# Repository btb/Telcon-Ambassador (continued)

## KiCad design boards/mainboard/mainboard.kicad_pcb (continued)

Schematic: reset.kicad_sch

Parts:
C26: C_Polarized_US; CP_Axial_L18.0mm_D10.0mm_P25.00mm_Horizontal
D17: 1N4148; D_DO-35_SOD27_P7.62mm_Horizontal
Q1, Q2, Q3: 2N3904; TO-92_Inline
R10, R11: 3.3K; R_Axial_DIN0309_L9.0mm_D3.2mm_P12.70mm_Horizontal
R12, R14: 680; R_Axial_DIN0309_L9.0mm_D3.2mm_P12.70mm_Horizontal
R13, R15: 150; R_Axial_DIN0309_L9.0mm_D3.2mm_P12.70mm_Horizontal
R171: 100; R_Axial_DIN0309_L9.0mm_D3.2mm_P12.70mm_Horizontal
R172: 47K; R_Axial_DIN0309_L9.0mm_D3.2mm_P12.70mm_Horizontal
U43: 7404; DIP-14_W7.62mm
U44: 12.5MHZ; Oscillator_DIP-14
U72: 7474; DIP-14_W7.62mm
U80: 7414; DIP-14_W7.62mm

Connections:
DBE: U80.4; also elsewhere on the board
GND: C26.2, Q1.1 (E), Q2.1 (E), Q3.1 (E), U44.7 (GND); also elsewhere on the board
unnamed: C26.1, D17.2 (A), Q1.2 (B), R171.1, R172.1
unnamed: Q1.3 (C), R10.2, R11.2, U80.11
unnamed: Q2.2 (B), R14.1
unnamed: Q3.2 (B), R12.1
unnamed: U43.13, U44.8 (OUT)
unnamed: R12.2, U72.5 (Q)
unnamed: R14.2, U72.6 (~Q), U80.1
OSC: U43.9, U43.11, U43.12; also elsewhere on the board
OSCB: U43.6; also elsewhere on the board
OSC/4: U72.3 (C); also elsewhere on the board
OSC/16: U72.2 (D); also elsewhere on the board
PHI1: Q2.3 (C), R15.2; also elsewhere on the board
PHI2: Q3.3 (C), R13.2; also elsewhere on the board
RESET: R11.1, U80.8; also elsewhere on the board
RESET_SW: R171.2; also elsewhere on the board
VCC: D17.1 (K), R10.1, R13.1, R15.1, R172.2, U44.14 (Vcc); also elsewhere on the board
~DBE: U80.2, U80.3; also elsewhere on the board
~OSCA: U43.10; also elsewhere on the board
~OSCB: U43.5, U43.8; also elsewhere on the board
~RESET: U80.9, U80.10; also elsewhere on the board

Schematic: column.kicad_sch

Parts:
RN3: 3.3K; R_Array_SIP10
U45: 74LS163; DIP-16_W7.62mm
U46: 74163; DIP-16_W7.62mm
U50: 7400; DIP-14_W7.62mm

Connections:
CBCLK: U46.7 (ENP), U46.10 (ENT); also elsewhere on the board
CC0: U46.14 (QA); also elsewhere on the board
CC1: U46.13 (QB); also elsewhere on the board
CC2: U46.12 (QC); also elsewhere on the board
CC3: U46.11 (QD); also elsewhere on the board
CC4: U45.14 (QA), U50.1; also elsewhere on the board
CC5: U45.13 (QB); also elsewhere on the board
CC6: U45.12 (QC), U50.2; also elsewhere on the board
GND: U45.3 (A), U45.4 (B), U45.5 (C), U45.6 (D), U45.8 (GND), U46.3 (A), U46.4 (B), U46.5 (C), U46.6 (D), U46.8 (GND); also elsewhere on the board
unnamed: RN3.5 (R4.2), U45.1 (~CLR), U46.1 (~CLR)
unnamed: U45.7 (ENP), U45.10 (ENT), U46.15 (RCO)
VCC: U45.16 (VCC), U46.16 (VCC); also elsewhere on the board
~OSCB: U45.2 (CLK), U46.2 (CLK); also elsewhere on the board
~POS79: U45.9 (~LOAD), U46.9 (~LOAD), U50.3; also elsewhere on the board

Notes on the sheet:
starts over from 0x00 at 01010000, 0x50, 80d

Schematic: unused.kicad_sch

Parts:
C1, C2, C3, C4, C5, C6, C7, C8, C9, C10, C11, C12, C13, C14, C15, C16, C17, C18, C19, C20, C21, C22, C27, C28, C29, C30, C31, C32, C33, C34, C35, C36, C37, C38, C39, C40, C41, C42, C43: 220nF; C_Disc_D4.3mm_W1.9mm_P6.35mm
RN3: 3.3K; R_Array_SIP10
RN4: R_Network09_Split; R_Array_SIP10
TP1: TestPoint; TestPoint_THTPad_1.0x1.0mm_Drill0.5mm
U10, U39, U53: 7408; DIP-14_W7.62mm
U11, U33, U50, U67: 7400; DIP-14_W7.62mm
U12, U43, U51, U75, U76: 7404; DIP-14_W7.62mm
U13, U14, U21: 74S139; DIP-16_W7.62mm
U34, U41, U63, U64, U65, U66, U72: 7474; DIP-14_W7.62mm
U38, U54: 7420; DIP-14_W7.62mm
U62: 7486; DIP-14_W7.62mm
U80: 7414; DIP-14_W7.62mm

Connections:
+12V: C15.1; also elsewhere on the board
-12V: C16.1; also elsewhere on the board
GND: C1.2, C2.2, C3.2, C4.2, C5.2, C6.2, C7.2, C8.2, C9.2, C10.2, C11.2, C12.2, C13.1, C14.2, C15.2, C16.2, C17.2, C18.2, C19.2, C20.1, C21.2, C22.2, C27.2, C28.1, C29.2, C30.2, C31.2, C32.2, C33.2, C34.2, C35.2, C36.2, C37.2, C38.2, C39.2, C40.2, C41.2, C42.2, C43.2, U10.7 (GND), U11.7 (GND), U12.7 (GND), U13.8 (GND), U14.8 (GND), U21.8 (GND), U33.7 (GND), U34.7 (GND), U38.7 (GND), U39.7 (GND), U41.7 (GND), U43.7 (GND), U50.7 (GND), U51.7 (GND), U53.7 (GND), U54.7 (GND), U62.7 (GND), U63.7 (GND), U64.7 (GND), U65.7 (GND), U66.7 (GND), U67.7 (GND), U72.7 (GND), U75.7 (GND), U76.7 (GND), U80.7 (GND); also elsewhere on the board
unnamed: RN3.10 (R9.2), TP1.1
VCC: C1.1, C2.1, C3.1, C4.1, C5.1, C6.1, C7.1, C8.1, C9.1, C10.1, C11.1, C12.1, C13.2, C14.1, C17.1, C18.1, C19.1, C20.2, C21.1, C22.1, C27.1, C28.2, C29.1, C30.1, C31.1, C32.1, C33.1, C34.1, C35.1, C36.1, C37.1, C38.1, C39.1, C40.1, C41.1, C42.1, C43.1, RN3.1 (R1.1), RN4.1 (R1.1), U10.14 (VCC), U11.14 (VCC), U12.14 (VCC), U13.16 (VCC), U14.16 (VCC), U21.16 (VCC), U33.14 (VCC), U34.14 (VCC), U38.14 (VCC), U39.14 (VCC), U41.14 (VCC), U43.14 (VCC), U50.14 (VCC), U51.14 (VCC), U53.14 (VCC), U54.14 (VCC), U62.14 (VCC), U63.14 (VCC), U64.14 (VCC), U65.14 (VCC), U66.14 (VCC), U67.14 (VCC), U72.14 (VCC), U75.14 (VCC), U76.14 (VCC), U80.14 (VCC); also elsewhere on the board

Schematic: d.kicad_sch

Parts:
RN1: R_Network09_US; R_Array_SIP10
U7: MC6800; DIP-40_W15.24mm
U8, U9: 74LS241; DIP-20_W7.62mm
U12: 7404; DIP-14_W7.62mm

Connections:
A0: U9.18 (O0a); also elsewhere on the board
A1: U9.3 (O3b); also elsewhere on the board
A2: U9.16 (O1a); also elsewhere on the board
A3: U8.3 (O3b); also elsewhere on the board
A4: U8.18 (O0a); also elsewhere on the board
A5: U9.14 (O2a); also elsewhere on the board
A6: U8.5 (O2b); also elsewhere on the board
A7: U8.16 (O1a); also elsewhere on the board
A8: U9.7 (O1b); also elsewhere on the board
A9: U8.7 (O1b); also elsewhere on the board
A10: U8.12 (O3a); also elsewhere on the board
A11: U8.9 (O0b); also elsewhere on the board
A12: U9.9 (O0b); also elsewhere on the board
A13: U9.12 (O3a); also elsewhere on the board
A14: U8.14 (O2a); also elsewhere on the board
A15: U9.5 (O2b); also elsewhere on the board
D0: U7.33 (D0); also elsewhere on the board
D1: U7.32 (D1); also elsewhere on the board
D2: U7.31 (D2); also elsewhere on the board
D3: U7.30 (D3); also elsewhere on the board
D4: U7.29 (D4); also elsewhere on the board
D5: U7.28 (D5); also elsewhere on the board
D6: U7.27 (D6); also elsewhere on the board
D7: U7.26 (D7); also elsewhere on the board
DBE: U7.36 (DBE); also elsewhere on the board
GND: U7.1 (VSS), U7.21 (VSS), U7.39 (TSC), U8.1 (OEa), U8.10 (GND), U9.1 (OEa), U9.10 (GND); also elsewhere on the board
unnamed: RN1.2 (R1), U7.2 (~HALT)
unnamed: RN1.6 (R5), U7.6 (~NMI)
unnamed: U7.9 (A0), U9.2 (I0a)
unnamed: U7.10 (A1), U9.17 (I3b)
unnamed: U7.11 (A2), U9.4 (I1a)
unnamed: U7.12 (A3), U8.17 (I3b)
unnamed: U7.13 (A4), U8.2 (I0a)
unnamed: U7.14 (A5), U9.6 (I2a)
unnamed: U7.15 (A6), U8.15 (I2b)
unnamed: U7.16 (A7), U8.4 (I1a)
unnamed: U7.17 (A8), U9.13 (I1b)
unnamed: U7.18 (A9), U8.13 (I1b)
unnamed: U7.19 (A10), U8.8 (I3a)
unnamed: U7.20 (A11), U8.11 (I0b)
unnamed: U7.22 (A12), U9.11 (I0b)
unnamed: U7.23 (A13), U9.8 (I3a)
unnamed: U7.24 (A14), U8.6 (I2a)
unnamed: U7.25 (A15), U9.15 (I2b)
unnamed: U7.34 (R/~W), U12.1
PHI1: U7.3 (Phi1); also elsewhere on the board
PHI2: U7.37 (Phi2); also elsewhere on the board
R/~W: U12.4; also elsewhere on the board
VCC: RN1.1 (common), U7.8 (VCC), U8.19 (OEb), U8.20 (VCC), U9.19 (OEb), U9.20 (VCC); also elsewhere on the board
VMA: U7.5 (VMA); also elsewhere on the board
~IRQ: RN1.4 (R3), U7.4 (~IRQ); also elsewhere on the board
~RESET: U7.40 (~RESET); also elsewhere on the board
~R/W: U12.2, U12.3; also elsewhere on the board

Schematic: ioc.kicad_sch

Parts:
D1: Conn_01x21; SolderWire-0.75sqmm_1x021_P3.96mm_D1.25mm_OD2.3mm
LS1: Speaker; Buzzer_15x7.5RM7.6
P1: Presets; DIP-16_W7.62mm
R2: 10; R_Axial_DIN0309_L9.0mm_D3.2mm_P12.70mm_Horizontal
R6, R7, R8: 220; R_Axial_DIN0309_L9.0mm_D3.2mm_P12.70mm_Horizontal
RN2: 3.3K; R_Array_SIP10
U70, U71: 6821; DIP-40_W15.24mm
U76: 7404; DIP-14_W7.62mm

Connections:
/IO/KBCON: D1.21, U70.39 (CA2)
/IO/KBD0: D1.12, U70.2 (PA0)
/IO/KBD1: D1.13, U70.3 (PA1)
/IO/KBD2: D1.14, U70.4 (PA2)
/IO/KBD3: D1.15, U70.5 (PA3)
/IO/KBD4: D1.16, U70.6 (PA4)
/IO/KBD5: D1.17, U70.7 (PA5)
/IO/KBD6: D1.18, U70.8 (PA6)
/IO/KBD7: D1.19, U70.9 (PA7)
/IO/KBINT: D1.20, U70.40 (CA1)
/IO/PA0: P1.4, RN2.2 (R1), U71.2 (PA0)
/IO/PRCON: D1.11, U70.19 (CB2)
/IO/PRD0: D1.2, U70.10 (PB0)
/IO/PRD1: D1.3, U70.11 (PB1)
/IO/PRD2: D1.4, U70.12 (PB2)
/IO/PRD3: D1.5, U70.13 (PB3)
/IO/PRD4: D1.6, U70.14 (PB4)
/IO/PRD5: D1.7, U70.15 (PB5)
/IO/PRD6: D1.8, U70.16 (PB6)
/IO/PRD7: D1.9, U70.17 (PB7)
/IO/PRINT: D1.10, U70.18 (CB1)
A0: U70.36 (RS0), U71.36 (RS0); also elsewhere on the board
A1: U70.35 (RS1), U71.35 (RS1); also elsewhere on the board
D0: U70.33 (D0), U71.33 (D0); also elsewhere on the board
D1: U70.32 (D1), U71.32 (D1); also elsewhere on the board
D2: U70.31 (D2), U71.31 (D2); also elsewhere on the board
D3: U70.30 (D3), U71.30 (D3); also elsewhere on the board
D4: U70.29 (D4), U71.29 (D4); also elsewhere on the board
D5: U70.28 (D5), U71.28 (D5); also elsewhere on the board
D6: U70.27 (D6), U71.27 (D6); also elsewhere on the board
D7: U70.26 (D7), U71.26 (D7); also elsewhere on the board
DBE: U70.25 (ENABLE), U71.25 (ENABLE); also elsewhere on the board
GND: D1.1, P1.2, P1.9, P1.10, U70.1 (VSS), U71.1 (VSS); also elsewhere on the board
IND4: R8.2; also elsewhere on the board
IND5: R6.2; also elsewhere on the board
IND6: R7.2; also elsewhere on the board
unnamed: LS1.2, R2.2
unnamed: P1.5, RN2.3 (R2), U71.3 (PA1)
unnamed: P1.6, RN2.8 (R7), U71.8 (PA6)
unnamed: P1.11, RN2.7 (R6), U71.7 (PA5)
unnamed: P1.12, RN2.6 (R5), U71.6 (PA4)
unnamed: P1.13, RN2.9 (R8), U71.9 (PA7)
unnamed: P1.14, RN2.5 (R4), U71.5 (PA3)
unnamed: P1.15, RN2.4 (R3), U71.4 (PA2)
unnamed: R2.1, U76.8
unnamed: R6.1, U76.4
unnamed: R7.1, U76.2
unnamed: R8.1, U76.6
unnamed: RN2.10 (R9), U71.39 (CA2)
unnamed: U71.10 (PB0), U76.3
unnamed: U71.11 (PB1), U76.1
unnamed: U71.12 (PB2), U76.5
unnamed: U71.13 (PB3), U76.11
unnamed: U76.9, U76.10
RXRDY: U71.18 (CB1); also elsewhere on the board
R/~W: U70.21 (R/~W), U71.21 (R/~W); also elsewhere on the board
TXRDY: U71.19 (CB2); also elsewhere on the board
VCC: LS1.1, P1.8, P1.16, RN2.1 (common), U70.20 (VCC), U70.22 (CS0), U70.24 (CS1), U71.20 (VCC), U71.22 (CS0), U71.24 (CS1); also elsewhere on the board
~IO_C_SEL: U71.23 (~CS2); also elsewhere on the board
~IO_D_SEL: U70.23 (~CS2); also elsewhere on the board
~IRQ: U70.37 (~IRQB), U70.38 (~IRQA), U71.37 (~IRQB), U71.38 (~IRQA); also elsewhere on the board
~RESET: U70.34 (~RESET), U71.34 (~RESET); also elsewhere on the board

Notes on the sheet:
PIN PRESET HI LO PA0 4 TTY NO YES PA1 5 BAUD 300 1200 PA2 15 STOP 1 2 PA3 14 PARITY N8 SEE PA4 PA4 12 PARITY E7 O7 PA5 11 DUPLEX PAGE SEE PA6 PA6 6 DUPLEX HALF FULL PA7 13 PRINTER ENABLED DISABLED

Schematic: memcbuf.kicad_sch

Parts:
U47: 6810; DIP-24_W15.24mm
U56: 74LS241; DIP-20_W7.62mm
U58, U59: 74175; DIP-16_W7.62mm
U66: 7474; DIP-14_W7.62mm
U67: 7400; DIP-14_W7.62mm

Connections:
/From Memory to Character Buffer/VRAM_R/~W: U47.16 (R/~W), U66.9 (Q), U67.4
CBCLK: U58.9 (Cp), U59.9 (Cp); also elsewhere on the board
CBUF1: U59.2 (Q0); also elsewhere on the board
CBUF2: U59.7 (Q1); also elsewhere on the board
CBUF3: U59.10 (Q2); also elsewhere on the board
CBUF4: U59.15 (Q3); also elsewhere on the board
CBUF5: U58.2 (Q0); also elsewhere on the board
CBUF6: U58.7 (Q1); also elsewhere on the board
CBUF7: U58.10 (Q2); also elsewhere on the board
CBUF8: U58.15 (Q3); also elsewhere on the board
CC0: U47.23 (A0); also elsewhere on the board
CC1: U47.22 (A1); also elsewhere on the board
CC2: U47.21 (A2); also elsewhere on the board
CC3: U47.20 (A3); also elsewhere on the board
CC4: U47.19 (A4); also elsewhere on the board
CC5: U47.18 (A5); also elsewhere on the board
CC6: U47.17 (A6); also elsewhere on the board
D0: U56.2 (I0a); also elsewhere on the board
D1: U56.4 (I1a); also elsewhere on the board
D2: U56.6 (I2a); also elsewhere on the board
D3: U56.8 (I3a); also elsewhere on the board
D4: U56.11 (I0b); also elsewhere on the board
D5: U56.13 (I1b); also elsewhere on the board
D6: U56.15 (I2b); also elsewhere on the board
D7: U56.17 (I3b); also elsewhere on the board
GND: U47.1 (GND), U47.11 (~CS1), U47.12 (~CS2), U47.14 (~CS4), U47.15 (~CS5), U56.10 (GND), U58.8 (GND), U59.8 (GND), U66.12 (D); also elsewhere on the board
unnamed: U47.13 (CS3), U67.6
unnamed: U47.2 (Q0), U56.18 (O0a), U59.4 (D0)
unnamed: U47.3 (Q1), U56.16 (O1a), U59.5 (D1)
unnamed: U47.4 (Q2), U56.14 (O2a), U59.12 (D2)
unnamed: U47.5 (Q3), U56.12 (O3a), U59.13 (D3)
unnamed: U47.6 (Q4), U56.9 (O0b), U58.4 (D0)
unnamed: U47.7 (Q5), U56.7 (O1b), U58.5 (D1)
unnamed: U47.8 (Q6), U56.5 (O2b), U58.12 (D2)
unnamed: U47.9 (Q7), U56.3 (O3b), U58.13 (D3)
U64: U56.1 (OEa); also elsewhere on the board
U66P6: U67.5; also elsewhere on the board
VCC: U47.10 (CS0), U47.24 (VCC), U56.20 (VCC), U58.16 (VCC), U59.16 (VCC); also elsewhere on the board
VRAM_EN: U66.11 (C); also elsewhere on the board
~DISP_EN: U66.10 (~S); also elsewhere on the board
~U64: U56.19 (OEb); also elsewhere on the board

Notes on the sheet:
128 bytes of RAM holds row of characters being currently sent to CRT

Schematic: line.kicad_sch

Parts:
RN3: 3.3K; R_Array_SIP10
U50: 7400; DIP-14_W7.62mm
U51: 7404; DIP-14_W7.62mm
U52: 74S138; DIP-16_W7.62mm
U53: 7408; DIP-14_W7.62mm
U54: 7420; DIP-14_W7.62mm
U55, U57: 74163; DIP-16_W7.62mm
U63: 7474; DIP-14_W7.62mm

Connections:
CBCLK: U50.8; also elsewhere on the board
GND: U52.4 (E1), U52.5 (E2), U52.8 (GND), U55.4 (B), U55.5 (C), U55.8 (GND), U57.3 (A), U57.8 (GND), U63.2 (D); also elsewhere on the board
HBLANK: U63.4 (~S); also elsewhere on the board
LC0: U54.1, U57.14 (QA); also elsewhere on the board
LC1: U54.2, U57.13 (QB); also elsewhere on the board
LC2: U54.4, U57.12 (QC); also elsewhere on the board
LC3: U51.1, U57.11 (QD); also elsewhere on the board
unnamed: RN3.7 (R6.2), U55.1 (~CLR), U55.6 (D), U55.7 (ENP), U55.10 (ENT)
unnamed: RN3.8 (R7.2), U57.1 (~CLR), U57.4 (B), U57.5 (C), U57.6 (D), U57.7 (ENP), U57.10 (ENT)
unnamed: U51.4, U54.5
unnamed: U51.12, U53.12
unnamed: U52.1 (A0), U55.14 (QA)
unnamed: U52.2 (A1), U55.13 (QB)
unnamed: U52.3 (A2), U55.12 (QC)
unnamed: U50.10, U52.14 (O1)
unnamed: U53.2, U54.6
unnamed: U51.13, U55.15 (RCO)
unnamed: U53.11, U55.9 (~LOAD)
unnamed: U57.2 (CLK), U63.6 (~Q)
unnamed: U51.3, U57.15 (RCO)
unnamed: U53.3, U57.9 (~LOAD)
OSC/16: U63.3 (C); also elsewhere on the board
VCC: U52.16 (VCC), U55.16 (VCC), U57.16 (VCC); also elsewhere on the board
~CCLK: U52.7 (O7); also elsewhere on the board
~DALOAD: U53.1; also elsewhere on the board
~DISP_EN: U50.9; also elsewhere on the board
~HBLANK: U53.13, U55.3 (A); also elsewhere on the board
~LC3: U51.2, U52.6 (E3); also elsewhere on the board
~LCCLK: U63.5 (Q); also elsewhere on the board
~OSCB: U55.2 (CLK); also elsewhere on the board

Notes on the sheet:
starts at 1110
load pixels from char rom to shift register U61
row of character (0-7)

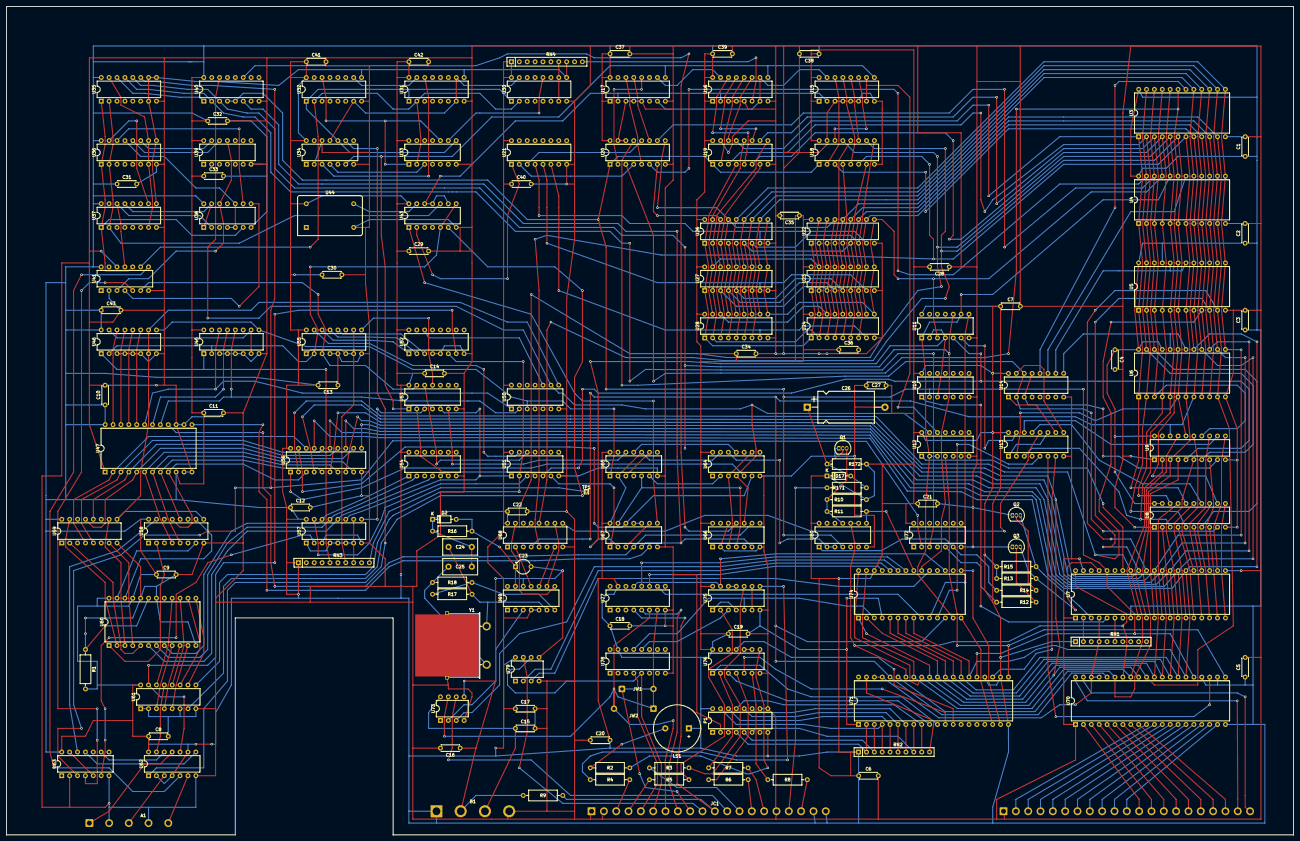
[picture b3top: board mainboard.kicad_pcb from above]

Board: 2 copper layers, 414.3 x 266.7 mm, 155 parts (0 on the bottom side), 301 nets.

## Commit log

2022-09-07 add roms
2022-09-07 add disassembly
2022-09-08 rename
2022-09-13 note incomplete character ROM
2022-09-13 add restored character ROM
2022-09-14 update disassembly
2022-09-19 more disassembly
2023-04-23 Add keyboard PCB project
2023-04-23 add 4592 datashet
2023-04-23 ignore
2023-04-24 simplify/correct keyboard schematics
2023-04-24 add 2758 datasheet
2023-04-24 keyboard schematic rev 1
2023-04-24 schematic pdf
2023-04-25 compress schematic
2023-04-25 add Makefile
2023-04-25 add Makefile for printer ROM
2023-04-25 add labels
2023-05-10 add printer schematic
2023-05-13 add mainboard schematic
2023-05-23 correct address
2023-05-27 disassembly
2023-05-27 organize mainboard schematic
2024-08-21 add missing bracket
2024-08-21 use correct label
2024-08-22 ignore generated rom images
2024-08-22 add datasheets
2024-08-22 Update to KiCad 8
2024-08-22 Add Ladouceur photos
2024-08-22 move roms to separate dir
2024-08-22 add printer specifications
2024-08-22 add photos
2024-08-22 add schematic pdfs
2024-09-16 document scancodes
2024-09-16 annotate the setup routines
2024-09-16 give names to last commands
2024-09-16 fix missing address
2024-09-16 document reset better
2024-09-16 annotate command codes
2024-09-26 don't need strings
2024-09-26 figured out f9dasm decimal display
2024-09-27 more dec fixes
